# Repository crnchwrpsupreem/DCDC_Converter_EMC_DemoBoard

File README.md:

# DCDC_Converter_EMC_DemoBoard
A testing board to learn about filtering / EMC, using a common Cheap DC/DC regulator (TI LM2596S)

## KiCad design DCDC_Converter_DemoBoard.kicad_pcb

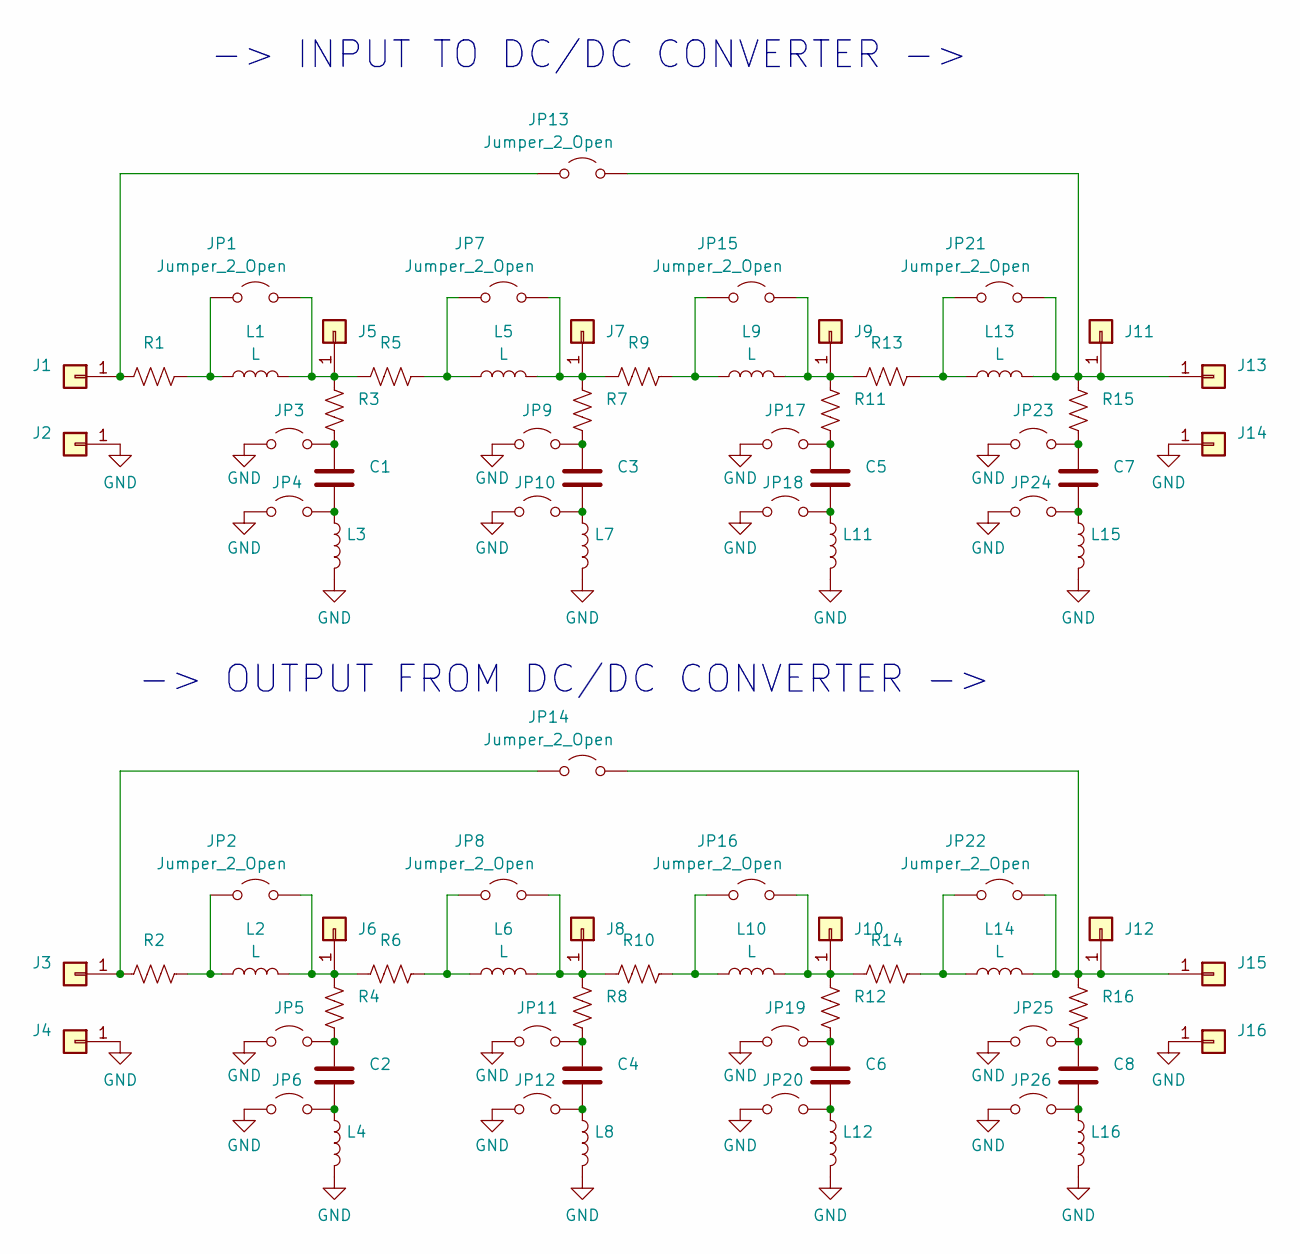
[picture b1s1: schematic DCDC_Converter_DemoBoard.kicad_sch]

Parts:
C1, C2, C3, C4, C5, C6, C7, C8: C; C_0805_2012Metric_Pad1.18x1.45mm_HandSolder
J1, J2, J3, J4, J5, J6, J7, J8, J9, J10, J11, J12, J13, J14, J15, J16: Conn_01x01; PinHeader_1x01_P2.54mm_Vertical
JP1, JP2, JP3, JP4, JP5, JP6, JP7, JP8, JP9, JP10, JP11, JP12, JP13, JP14, JP15, JP16, JP17, JP18, JP19, JP20, JP21, JP22, JP23, JP24, JP25, JP26: Jumper_2_Open; PinHeader_1x02_P2.54mm_Vertical
L1, L2, L5, L6, L9, L10, L13, L14: L; L_10.4x10.4_H4.8
L3, L4, L7, L8, L11, L12, L15, L16: L; L_1812_4532Metric_Pad1.30x3.40mm_HandSolder
R1, R2, R3, R4, R5, R6, R7, R8, R9, R10, R11, R12, R13, R14, R15, R16: R_US; R_0805_2012Metric_Pad1.20x1.40mm_HandSolder

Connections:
GND: J2.1, J4.1, J14.1, J16.1, JP3.1 (A), JP4.1 (A), JP5.1 (A), JP6.1 (A), JP9.1 (A), JP10.1 (A), JP11.1 (A), JP12.1 (A), JP17.1 (A), JP18.1 (A), JP19.1 (A), JP20.1 (A), JP23.1 (A), JP24.1 (A), JP25.1 (A), JP26.1 (A), L3.2, L4.2, L7.2, L8.2, L11.2, L12.2, L15.2, L16.2
unnamed: J1.1, JP13.1 (A), R1.1
unnamed: J3.1, JP14.1 (A), R2.1
unnamed: J5.1, JP1.2 (B), L1.2, R3.1, R5.1
unnamed: J6.1, JP2.2 (B), L2.2, R4.1, R6.1
unnamed: J7.1, JP7.2 (B), L5.2, R7.1, R9.1
unnamed: J8.1, JP8.2 (B), L6.2, R8.1, R10.1
unnamed: J9.1, JP15.2 (B), L9.2, R11.1, R13.1
unnamed: J10.1, JP16.2 (B), L10.2, R12.1, R14.1
unnamed: J11.1, J13.1, JP13.2 (B), JP21.2 (B), L13.2, R15.1
unnamed: J12.1, J15.1, JP14.2 (B), JP22.2 (B), L14.2, R16.1
unnamed: JP1.1 (A), L1.1, R1.2
unnamed: JP2.1 (A), L2.1, R2.2
unnamed: C1.1, JP3.2 (B), R3.2
unnamed: C1.2, JP4.2 (B), L3.1
unnamed: C2.1, JP5.2 (B), R4.2
unnamed: C2.2, JP6.2 (B), L4.1
unnamed: JP7.1 (A), L5.1, R5.2
unnamed: JP8.1 (A), L6.1, R6.2
unnamed: C3.1, JP9.2 (B), R7.2
unnamed: C3.2, JP10.2 (B), L7.1
unnamed: C4.1, JP11.2 (B), R8.2
unnamed: C4.2, JP12.2 (B), L8.1
unnamed: JP15.1 (A), L9.1, R9.2
unnamed: JP16.1 (A), L10.1, R10.2
unnamed: C5.1, JP17.2 (B), R11.2
unnamed: C5.2, JP18.2 (B), L11.1
unnamed: C6.1, JP19.2 (B), R12.2
unnamed: C6.2, JP20.2 (B), L12.1
unnamed: JP21.1 (A), L13.1, R13.2
unnamed: JP22.1 (A), L14.1, R14.2
unnamed: C7.1, JP23.2 (B), R15.2
unnamed: C7.2, JP24.2 (B), L15.1
unnamed: C8.1, JP25.2 (B), R16.2
unnamed: C8.2, JP26.2 (B), L16.1

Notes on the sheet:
-> OUTPUT FROM DC/DC CONVERTER ->
-> INPUT TO DC/DC CONVERTER ->

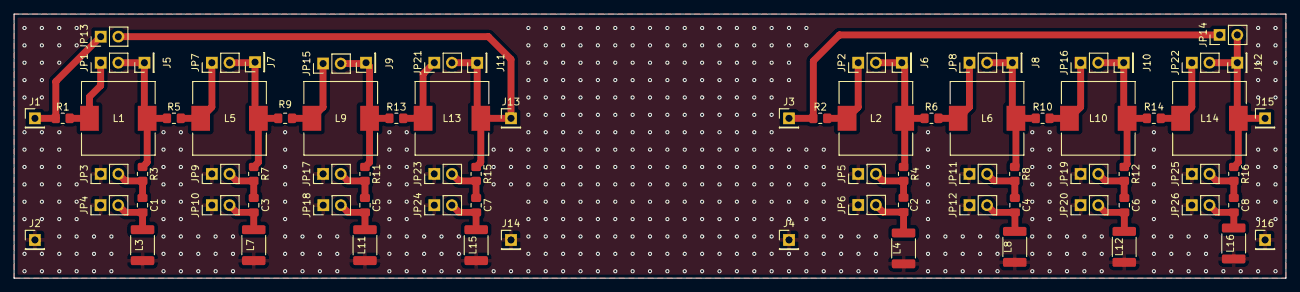
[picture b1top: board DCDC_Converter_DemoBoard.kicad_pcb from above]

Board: 2 copper layers, 183.0 x 38.0 mm, 82 parts (0 on the bottom side), 35 nets.

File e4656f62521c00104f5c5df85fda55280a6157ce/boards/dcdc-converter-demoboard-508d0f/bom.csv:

Designator,Footprint,Quantity,Value,LCSC Part #
"C1, C2, C3, C4, C5, C6, C7, C8",0805,8,C,
"J1, J10, J11, J12, J13, J14, J15, J16, J2, J3, J4, J5, J6, J7, J8, J9",PinHeader_1x01_P2.54mm_Vertical,16,Conn_01x01,
"JP1, JP10, JP11, JP12, JP13, JP14, JP15, JP16, JP17, JP18, JP19, JP2, JP20, JP21, JP22, JP23, JP24, JP25, JP26, JP3, JP4, JP5, JP6, JP7, JP8, JP9",PinHeader_1x02_P2.54mm_Vertical,26,Jumper_2_Open,
"L1, L10, L13, L14, L2, L5, L6, L9",L_10.4x10.4_H4.8,8,L,
"L11, L12, L15, L16, L3, L4, L7, L8",1812,8,L,
"R1, R10, R11, R12, R13, R14, R15, R16, R2, R3, R4, R5, R6, R7, R8, R9",0805,16,R_US,

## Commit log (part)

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2025-11-02 completed first version of schematic, pending changes after some design review
2025-11-05 completed board layout and exported gerbers
2025-11-05 fixed footprint and cleaned up silkscreen
